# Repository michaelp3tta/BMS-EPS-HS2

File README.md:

# BMS-EPS-HS2
Repository of the HS-2 Battery Management System

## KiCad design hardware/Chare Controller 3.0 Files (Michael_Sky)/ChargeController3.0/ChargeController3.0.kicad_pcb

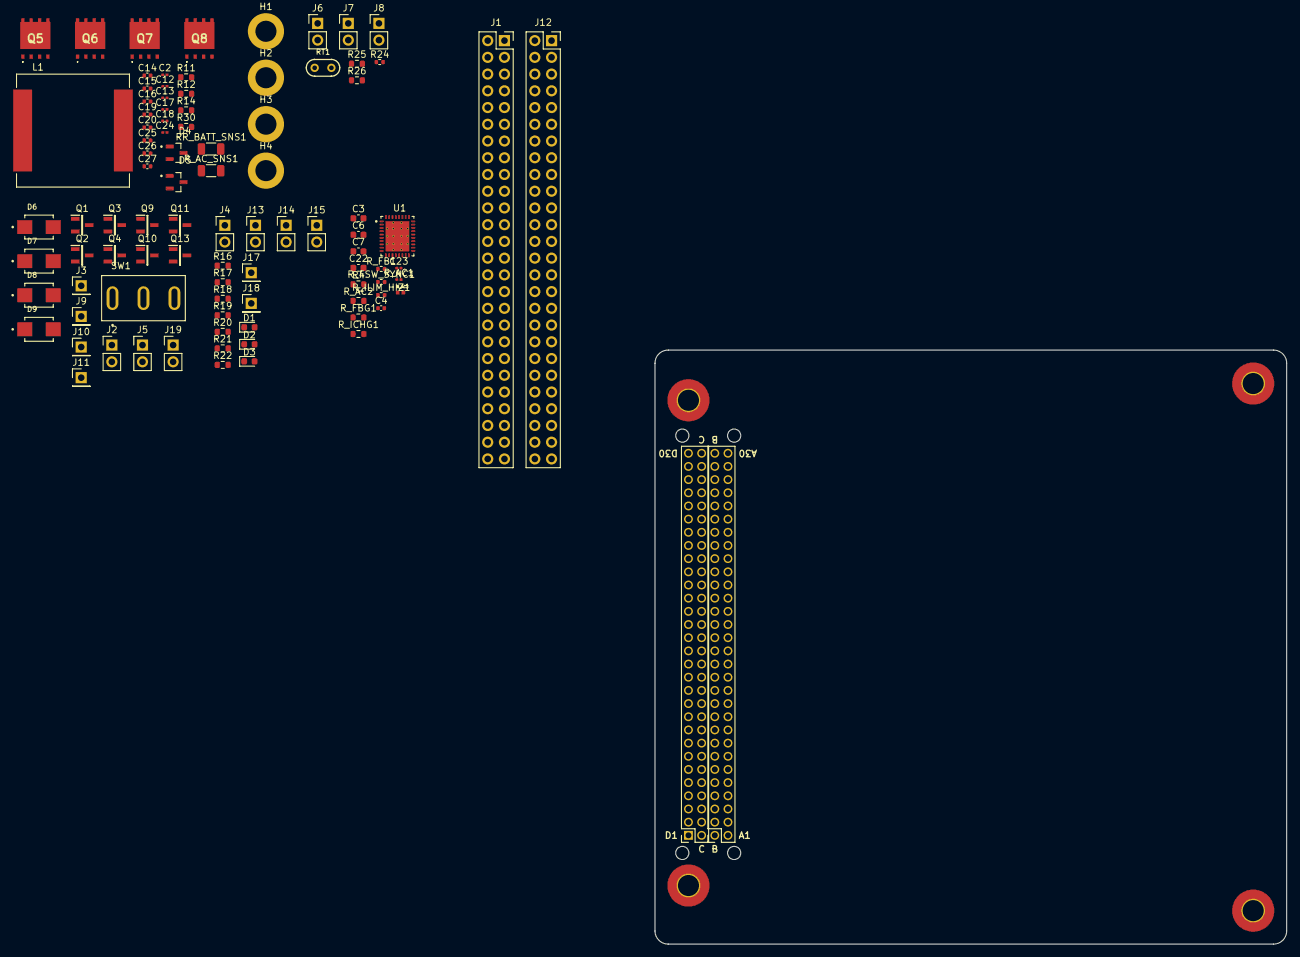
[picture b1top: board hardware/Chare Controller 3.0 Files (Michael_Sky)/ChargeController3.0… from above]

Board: 2 copper layers, 95.9 x 90.2 mm, 102 parts (0 on the bottom side), 56 nets, no tracks yet.

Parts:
C2, C12, C13, C17, C18, C24: 56u; C_0201_0603Metric
C3, C7, C22: 4.7u; C_0603_1608Metric
C4, C14, C16, C19, C20, C25, C27: 100n; C_0402_1005Metric
C6: 47u; C_0603_1608Metric
C15, C26: 470n; C_0402_1005Metric
C23: 1u; C_0201_0603Metric
D1, D2, D3: GREEN; LED_0603_1608Metric
D4, D5: BAT54
D6, D7, D8, D9: SS24
H1, H2, H3, H4: MountingHole_Pad; MountingHole_3.2mm_M3_ISO14580_Pad
H1#2, H2#2, H3#2, H4#2: MountingHole_Pad; MountingHole_3.2mm_M3_Pad_TopBottom
H5, H6, H7, H8: MountingHole; MountingHole_2mm
J1, J2: Conn_02x30_Row_Letter_First; PinSocket_2x30_P2.00mm_Vertical
J1#2, J12: Conn_02x26_Odd_Even; PinSocket_2x26_P2.54mm_Vertical
J2#2: SP_01x02_Pin; PinHeader_1x02_P2.54mm_Vertical
J3: BATT_TEST_01x01_Pin; PinHeader_1x01_P2.54mm_Vertical
J4: 3.3V_PULLUP_01x02_Pin; PinHeader_1x02_P2.54mm_Vertical
J5: BATT_01x02_Pin; PinHeader_1x02_P2.54mm_Vertical
J6, J7, J8, J13, J14, J15: Conn-1x2; PinHeader_1x02_P2.54mm_Vertical
J9: SYS_TEST_01x01_Pin; PinHeader_1x01_P2.54mm_Vertical
J10: SOL_TEST_01x01_Pin; PinHeader_1x01_P2.54mm_Vertical
J11: GND_TEST_01x01_Pin; PinHeader_1x01_P2.54mm_Vertical
J17: SCL_MAS_01x01_Pin; PinHeader_1x01_P2.54mm_Vertical
J18: SDA_MAS_01x01_Pin; PinHeader_1x01_P2.54mm_Vertical
J19: SYS-1x2; PinHeader_1x02_P2.54mm_Vertical
L1: IHLP6767GZER100M01; IND_IHLP6767GZER100M01
Q1, Q2, Q3, Q4, Q9, Q10, Q11, Q13: SI2318CDS-T1-GE3
Q5, Q6, Q7, Q8: AONS66614; AON6482
R4, R11, R12, R14, R30: 10; R_0603_1608Metric
R16, R17, R18, R19, R20, R21, R22, R26: 10k; R_0603_1608Metric
R24: 30.1k; R_0402_1005Metric
R25: 5.23k; R_0603_1608Metric
RR_BATT_SNS1: 5m; R_1206_3216Metric
RT1: 103AT-2
R_AC1: 1M; R_0201_0603Metric
R_AC2: 11.83k; R_0603_1608Metric
R_AC3: RC0402FR-0753K6L
R_AC_SNS1: 5m; R_1206_3216Metric
R_FB1: 249k; R_0402_1005Metric
R_FBG1: 16.67k; R_0603_1608Metric
R_FSW_SYNC1: 40k; R_0402_1005Metric
R_ICHG1: 16.67k; R_0603_1608Metric
R_ILIM_HIZ1: 25k; R_0402_1005Metric
SW1: 100SP1T1B1M1QEH; SW_100SP1T1B1M1QEH
U1: BQ25756ERRVR; IC_BQ25756ERRVR

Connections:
5V_PERM: J1#2.25, J1#2.26, J12.25, J12.26
/BQ25756E/ACOV: R_AC2.2, R_AC3.1, U1.35 (ACOV)
/BQ25756E/ACUV: R_AC1.2, R_AC2.1, U1.34 (ACUV)
/BQ25756E/FB: R_FB1.2, R_FBG1.1, U1.12 (FB)
/BQ25756E/FBG: R_FBG1.2, U1.11 (FBG)
/Inhibits, Inputs/EN: Q1.1, Q2.1, Q3.1, Q4.1, Q9.1, Q10.1, Q11.1, Q13.1, SW1.1
ACN: C26.2, C27.2, R30.2, U1.29 (ACN)
ACP: C25.2, C26.1, R11.2, U1.30 (ACP)
BTST_1: C19.2, D5.3, U1.26 (BTST1)
BTST_2: C20.2, D4.3, U1.20 (BTST2)
CE: J13.2, R18.1, U1.7 (~CE)
CHARGE: J1#2.31, J1#2.32
DRV_SUP: C3.1, C22.1, D4.1, D5.1, J7.1, U1.23 (DRV_SUP), U1.24 (REGN)
GND: C2.2, C3.2, C4.2, C6.2, C7.2, C12.2, C13.2, C14.1, C16.1, C17.2, C18.2, C22.2, C23.2, C24.2, C25.1, C27.1, H1.1, H1#2.1, H2.1, H2#2.1, H3.1, H3#2.1, H4.1, H4#2.1, J1#2.33, J1#2.34, J2#2.2, J4.2, J8.2, J11.1, J12.29, J12.30, J12.31, J12.32, J13.1, J19.2, Q7.1 (S_1), Q7.2 (S_2), Q7.3 (S_3), Q8.1 (S_1), Q8.2 (S_2), Q8.3 (S_3), Q9.3, Q13.2, R24.1, R26.1, R_AC3.2, R_FSW_SYNC1.1, R_ICHG1.1, R_ILIM_HIZ1.1, SW1.3
HIDRV_1: Q5.4 (G), U1.27 (HIDRV1)
HIDRV_2: Q6.4 (G), U1.19 (HIDRV2)
INT: J14.1, U1.3 (~INT)
LODRV_1: Q7.4 (G), U1.25 (LODRV1)
LODRV_2: Q8.4 (G), U1.21 (LODRV2)
unnamed: C6.1, R4.2
unnamed: D1.2 (A), R19.1
unnamed: D2.2 (A), R21.1
unnamed: D2.1 (K), J15.2
unnamed: D3.2 (A), R22.1
unnamed: D6.C, D7.A, Q1.3
unnamed: D7.C, D9.C, SW1.2
unnamed: D8.C, D9.A
unnamed: J4.1, R16.2, R17.2, R18.2, R19.2, R20.2, R21.2, R22.2
unnamed: J5.2, Q4.3
unnamed: J6.2, R26.2
unnamed: J7.2, R25.2
unnamed: J8.1, RT1.2
unnamed: D6.A, J2#2.1, J10.1
unnamed: J14.2, R20.1
unnamed: J9.1, J19.1, Q10.3
unnamed: Q1.2, Q2.3
unnamed: Q4.2, Q9.2
unnamed: C12.1, Q5.5 (D_1), Q5.6 (D_2), Q5.7 (D_3), Q5.8 (D_4), Q5.9 (D_5), R30.1, R_AC_SNS1.1
unnamed: C24.1, Q6.5 (D_1), Q6.6 (D_2), Q6.7 (D_3), Q6.8 (D_4), Q6.9 (D_5), R12.1, RR_BATT_SNS1.2
unnamed: Q10.2, Q11.2
unnamed: R_FSW_SYNC1.2, U1.36 (FSW_SYNC)
unnamed: R_ICHG1.2, U1.9 (ICHG)
unnamed: R_ILIM_HIZ1.2, U1.10 (ILIM_HIZ)
PG: D1.1 (K), U1.6 (~PG)
PGND: Q13.3, U1.17 (PGND), U1.22 (PGND), U1.37 (PGND)
SCL: J1#2.10, J17.1, R16.1, U1.1 (SCL)
SDA: J18.1, R17.1, U1.2 (SDA)
SOL: C2.1, C4.1, C7.1, C13.1, C23.1, J12.44, Q2.2, Q3.2, R4.1, R11.1, R_AC1.1, R_AC_SNS1.2, U1.32 (VAC), U1.33 (VAC)
SRN: C15.2, C16.2, R14.2, U1.13 (SRN)
SRP: C14.2, C15.1, R12.2, U1.14 (SRP)
STAT_1: J15.1, U1.4 (STAT1)
STAT_2: D3.1 (K), U1.5 (STAT2)
SW1: C19.1, L1.1, Q5.1 (S_1), Q5.2 (S_2), Q5.3 (S_3), Q7.5 (D_1), Q7.6 (D_2), Q7.7 (D_3), Q7.8 (D_4), Q7.9 (D_5), U1.28 (SW1)
SW2: C20.1, L1.2, Q6.1 (S_1), Q6.2 (S_2), Q6.3 (S_3), Q8.5 (D_1), Q8.6 (D_2), Q8.7 (D_3), Q8.8 (D_4), Q8.9 (D_5), U1.18 (SW2)
SYS/BATT: C17.1, C18.1, D8.A, J3.1, J5.1, J12.46, Q3.3, Q11.3, R14.1, RR_BATT_SNS1.1, R_FB1.1
TS: J6.1, R24.2, R25.1, RT1.1, U1.8 (TS)

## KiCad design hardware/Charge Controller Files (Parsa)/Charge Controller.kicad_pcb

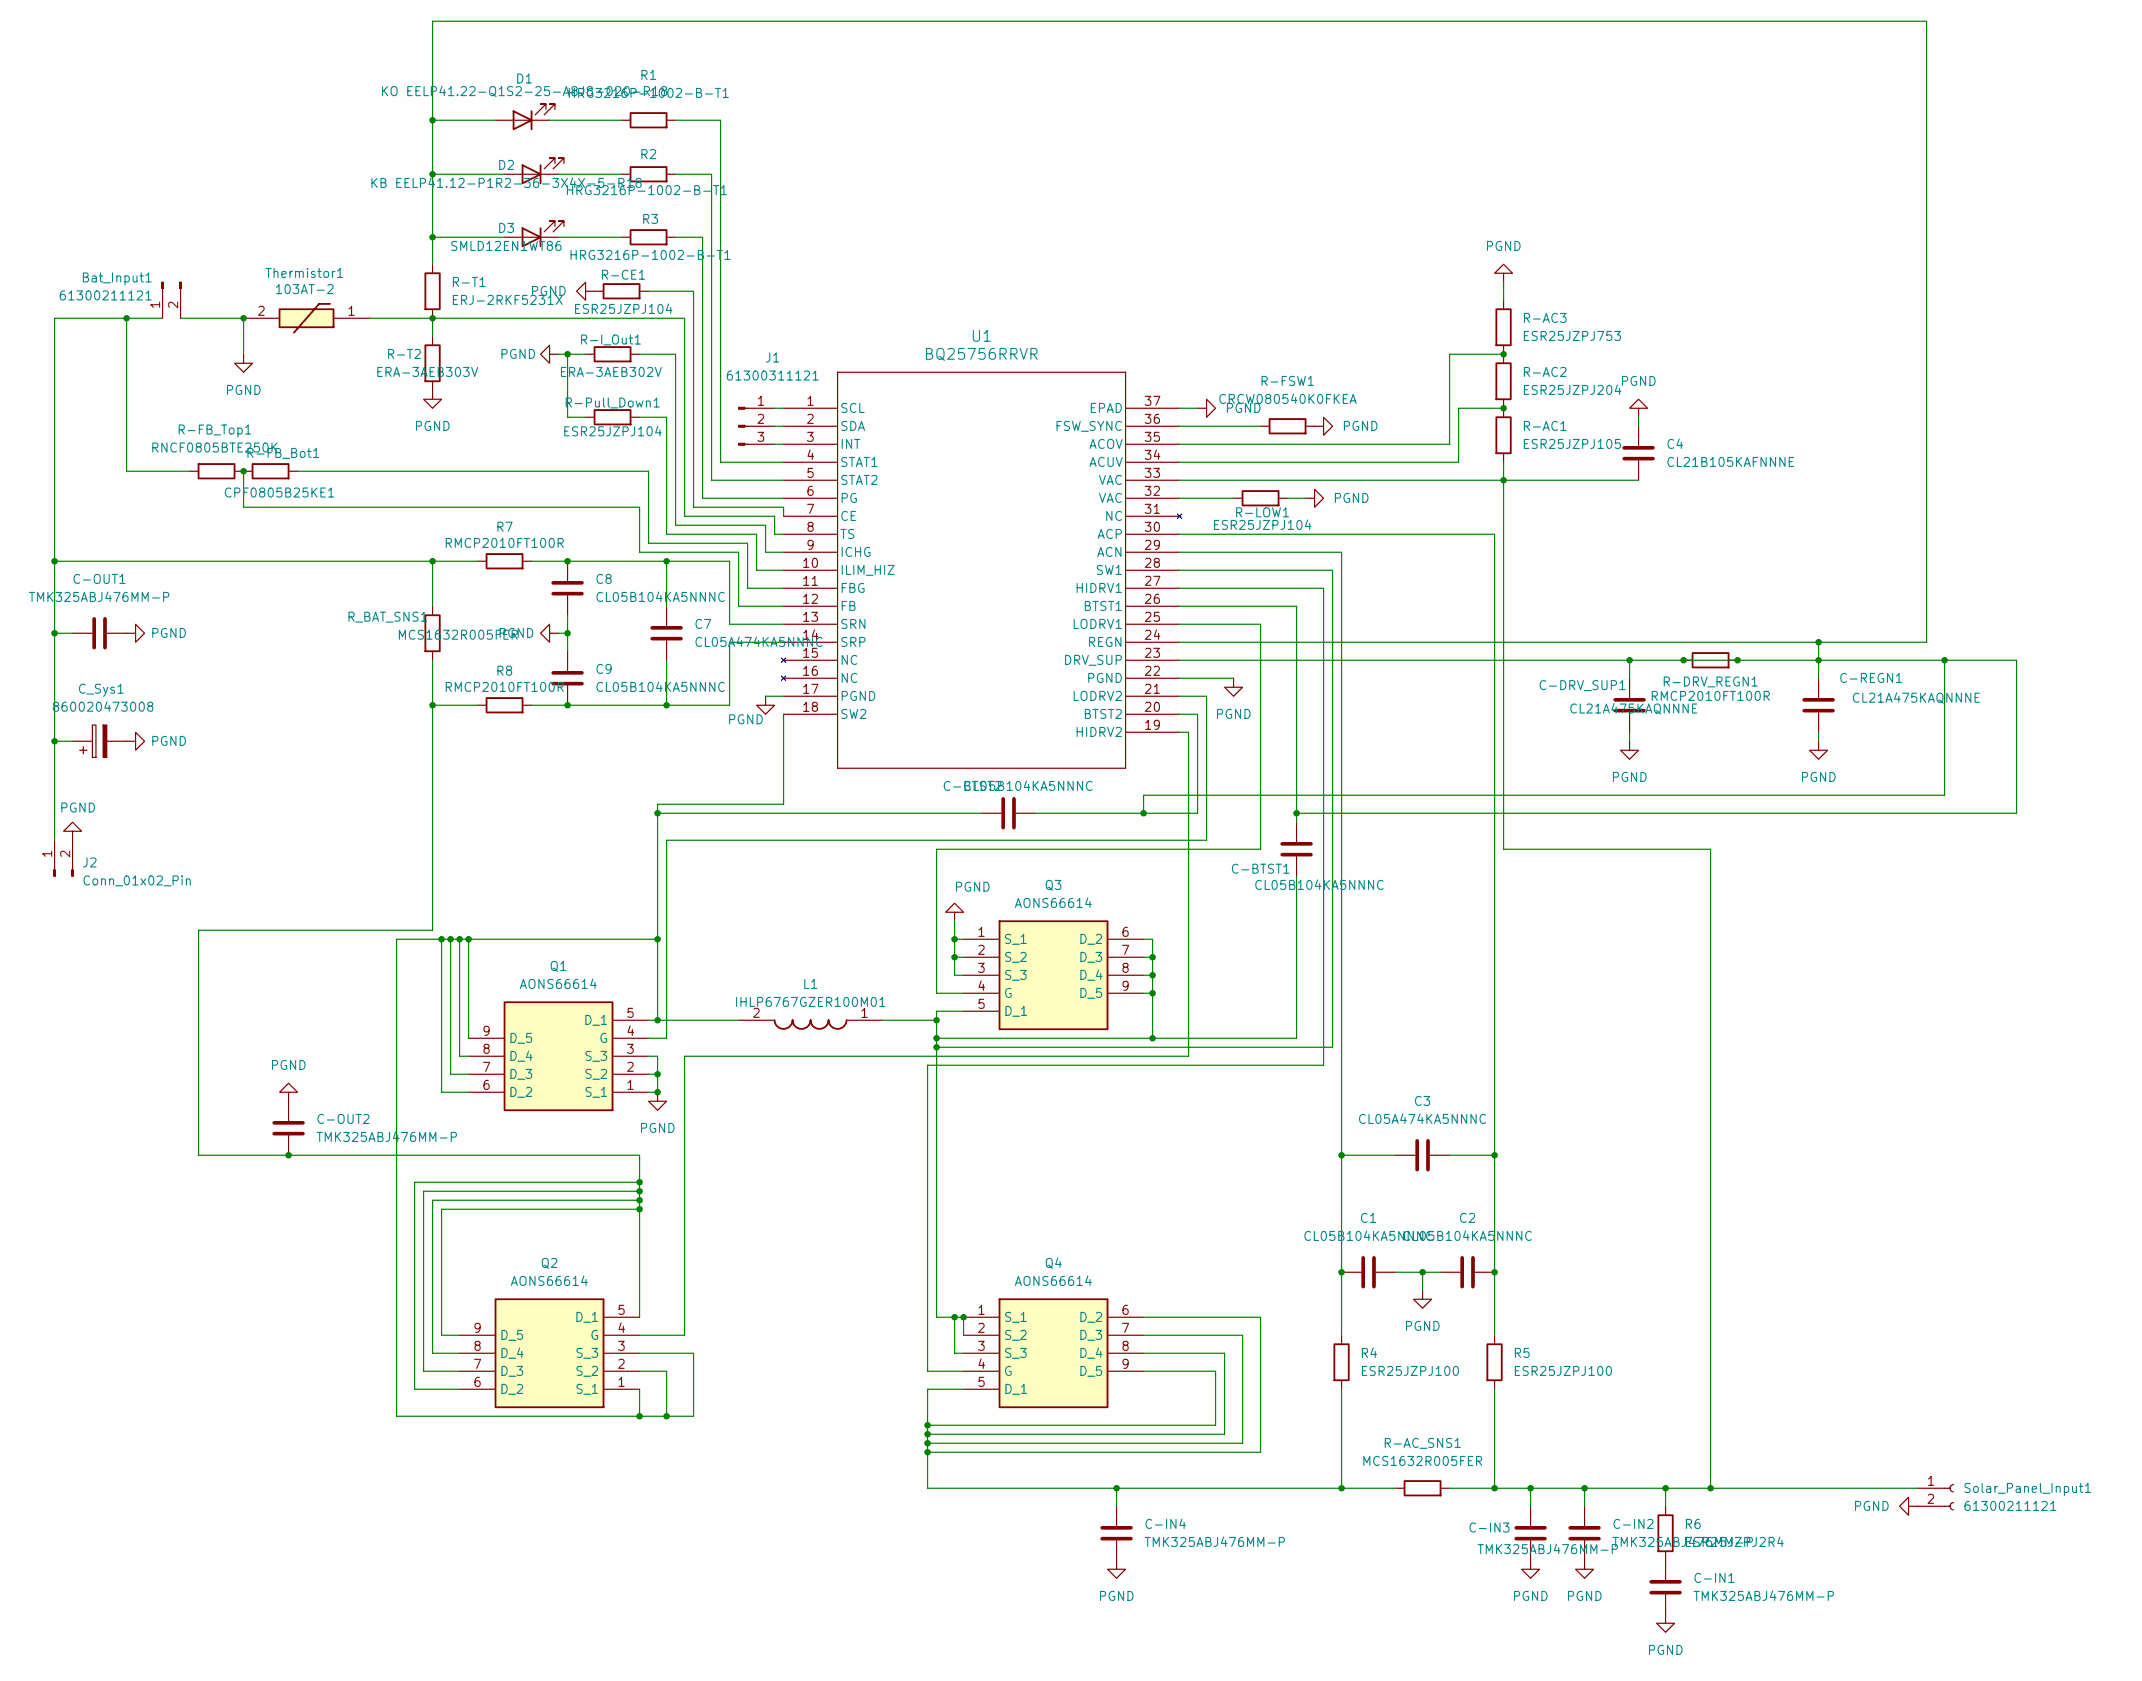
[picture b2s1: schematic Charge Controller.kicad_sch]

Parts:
Bat_Input1: 61300211121; PinHeader_1x02_P2.54mm_Vertical
C1, C2, C8, C9: CL05B104KA5NNNC; C_0402_1005Metric_Pad0.74x0.62mm_HandSolder
C3, C7: CL05A474KA5NNNC; C_0402_1005Metric_Pad0.74x0.62mm_HandSolder
C4: CL21B105KAFNNNE; C_0805_2012Metric_Pad1.18x1.45mm_HandSolder
C-BTST1, C-BTST2: CL05B104KA5NNNC; C_0402_1005Metric_Pad0.74x0.62mm_HandSolder
C-DRV_SUP1: CL21A475KAQNNNE; C_0805_2012Metric_Pad1.18x1.45mm_HandSolder
C-IN1, C-IN2, C-IN3, C-IN4: TMK325ABJ476MM-P; C_1210_3225Metric_Pad1.33x2.70mm_HandSolder
C-OUT1, C-OUT2: TMK325ABJ476MM-P; C_1210_3225Metric_Pad1.33x2.70mm_HandSolder
C-REGN1: CL21A475KAQNNNE; C_0805_2012Metric_Pad1.18x1.45mm_HandSolder
C_Sys1: 860020473008; CP_Radial_D6.3mm_P2.50mm
D1: KO EELP41.22-Q1S2-25-A8J8-020-R18; LED_0603_1608Metric_Pad1.05x0.95mm_HandSolder
D2: KB EELP41.12-P1R2-36-3X4X-5-R18; LED_0603_1608Metric_Pad1.05x0.95mm_HandSolder
D3: SMLD12EN1WT86; LED_0603_1608Metric_Pad1.05x0.95mm_HandSolder
J1: 61300311121; PinSocket_1x03_P2.54mm_Vertical
J2: Conn_01x02_Pin; PinSocket_1x02_P2.54mm_Vertical
L1: IHLP6767GZER100M01; INDPM172172X700N; Manufacturer_Part_Number IHLP6767GZER100M01
Q1, Q2, Q3, Q4: AONS66614; AON6482; Manufacturer_Part_Number AONS66614
R1, R2, R3: HRG3216P-1002-B-T1; R_1206_3216Metric_Pad1.30x1.75mm_HandSolder
R4, R5: ESR25JZPJ100; R_1210_3225Metric_Pad1.30x2.65mm_HandSolder
R6: ESR25JZPJ2R4; R_1210_3225Metric_Pad1.30x2.65mm_HandSolder
R7, R8: RMCP2010FT100R; R_2010_5025Metric_Pad1.40x2.65mm_HandSolder
R-AC1: ESR25JZPJ105; R_1210_3225Metric_Pad1.30x2.65mm_HandSolder
R-AC2: ESR25JZPJ204; R_1210_3225Metric_Pad1.30x2.65mm_HandSolder
R-AC3: ESR25JZPJ753; R_1210_3225Metric_Pad1.30x2.65mm_HandSolder
R-AC_SNS1: MCS1632R005FER; R_1206_3216Metric_Pad1.30x1.75mm_HandSolder
R-CE1: ESR25JZPJ104; R_1210_3225Metric_Pad1.30x2.65mm_HandSolder
R-DRV_REGN1: RMCP2010FT100R; R_2010_5025Metric_Pad1.40x2.65mm_HandSolder
R-FB_Bot1: CPF0805B25KE1; R_0805_2012Metric_Pad1.20x1.40mm_HandSolder
R-FB_Top1: RNCF0805BTE250K; R_0805_2012Metric_Pad1.20x1.40mm_HandSolder
R-FSW1: CRCW080540K0FKEA; R_0805_2012Metric_Pad1.20x1.40mm_HandSolder
R-I_Out1: ERA-3AEB302V; R_0603_1608Metric_Pad0.98x0.95mm_HandSolder
R-LOW1: ESR25JZPJ104; R_1210_3225Metric_Pad1.30x2.65mm_HandSolder
R-Pull_Down1: ESR25JZPJ104; R_1210_3225Metric_Pad1.30x2.65mm_HandSolder
R-T1: ERJ-2RKF5231X; R_0402_1005Metric_Pad0.72x0.64mm_HandSolder
R-T2: ERA-3AEB303V; R_0603_1608Metric_Pad0.98x0.95mm_HandSolder
R_BAT_SNS1: MCS1632R005FER; R_1206_3216Metric_Pad1.30x1.75mm_HandSolder
Solar_Panel_Input1: 61300211121; PinSocket_1x02_P2.54mm_Vertical
Thermistor1: 103AT-2; 103AT2; Mouser Part Number 954-103AT-2
U1: BQ25756RRVR; VQFN36_RRV_TEX

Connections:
unnamed: Bat_Input1.1, C-OUT1.1, C_Sys1.1, J2.1, R7.1, R-FB_Top1.2, R_BAT_SNS1.1
unnamed: C-IN1.1, R6.2
unnamed: C-BTST1.1, C-BTST2.2, C-DRV_SUP1.1, C-REGN1.1, D1.2 (A), D2.2 (A), D3.2 (A), R-DRV_REGN1.1, R-DRV_REGN1.2, R-T1.1, U1.20 (BTST2), U1.23 (DRV_SUP), U1.24 (REGN), U1.26 (BTST1)
unnamed: D1.1 (K), R1.1
unnamed: D2.1 (K), R2.1
unnamed: D3.1 (K), R3.1
unnamed: J1.1, U1.1 (SCL)
unnamed: J1.2, U1.2 (SDA)
unnamed: J1.3, U1.3 (INT)
unnamed: C-BTST2.1, L1.2, Q1.5 (D_1), Q1.6 (D_2), Q1.7 (D_3), Q1.8 (D_4), Q1.9 (D_5), Q2.1 (S_1), Q2.2 (S_2), Q2.3 (S_3), U1.18 (SW2)
unnamed: Q1.4 (G), U1.21 (LODRV2)
unnamed: C-OUT2.2, Q2.5 (D_1), Q2.6 (D_2), Q2.7 (D_3), Q2.8 (D_4), Q2.9 (D_5), R8.1, R_BAT_SNS1.2
unnamed: Q2.4 (G), U1.19 (HIDRV2)
unnamed: C-BTST1.2, L1.1, Q3.5 (D_1), Q3.6 (D_2), Q3.7 (D_3), Q3.8 (D_4), Q3.9 (D_5), Q4.1 (S_1), Q4.2 (S_2), Q4.3 (S_3), U1.28 (SW1)
unnamed: Q3.4 (G), U1.25 (LODRV1)
unnamed: C-IN4.2, Q4.5 (D_1), Q4.6 (D_2), Q4.7 (D_3), Q4.8 (D_4), Q4.9 (D_5), R4.2, R-AC_SNS1.1
unnamed: Q4.4 (G), U1.27 (HIDRV1)
unnamed: R-LOW1.1, U1.32 (VAC)
unnamed: C4.2, C-IN2.1, C-IN3.1, R5.2, R6.1, R-AC1.2, R-AC_SNS1.2, Solar_Panel_Input1.1, U1.33 (VAC)
unnamed: C1.1, C3.1, R4.1, U1.29 (ACN)
unnamed: R-AC2.1, R-AC3.2, U1.35 (ACOV)
unnamed: C2.2, C3.2, R5.1, U1.30 (ACP)
unnamed: R-AC1.1, R-AC2.2, U1.34 (ACUV)
unnamed: R-CE1.2, U1.7 (CE)
unnamed: R-FB_Bot1.1, R-FB_Top1.1, U1.12 (FB)
unnamed: R-FB_Bot1.2, U1.11 (FBG)
unnamed: R-FSW1.1, U1.36 (FSW_SYNC)
unnamed: R-I_Out1.2, U1.9 (ICHG)
unnamed: R-Pull_Down1.2, U1.10 (ILIM_HIZ)
unnamed: R3.2, U1.6 (PG)
unnamed: C7.1, C8.1, R7.2, U1.13 (SRN)
unnamed: C7.2, C9.2, R8.2, U1.14 (SRP)
unnamed: R1.2, U1.4 (STAT1)
unnamed: R2.2, U1.5 (STAT2)
unnamed: R-T1.2, R-T2.1, Thermistor1.1, U1.8 (TS)
PGND: Bat_Input1.2, C1.2, C2.1, C4.1, C8.2, C9.1, C-DRV_SUP1.2, C-IN1.2, C-IN2.2, C-IN3.2, C-IN4.1, C-OUT1.2, C-OUT2.1, C-REGN1.2, C_Sys1.2, J2.2, Q1.1 (S_1), Q1.2 (S_2), Q1.3 (S_3), Q3.1 (S_1), Q3.2 (S_2), Q3.3 (S_3), R-AC3.1, R-CE1.1, R-FSW1.2, R-I_Out1.1, R-LOW1.2, R-Pull_Down1.1, R-T2.2, Solar_Panel_Input1.2, Thermistor1.2, U1.17 (PGND), U1.22 (PGND), U1.37 (EPAD)

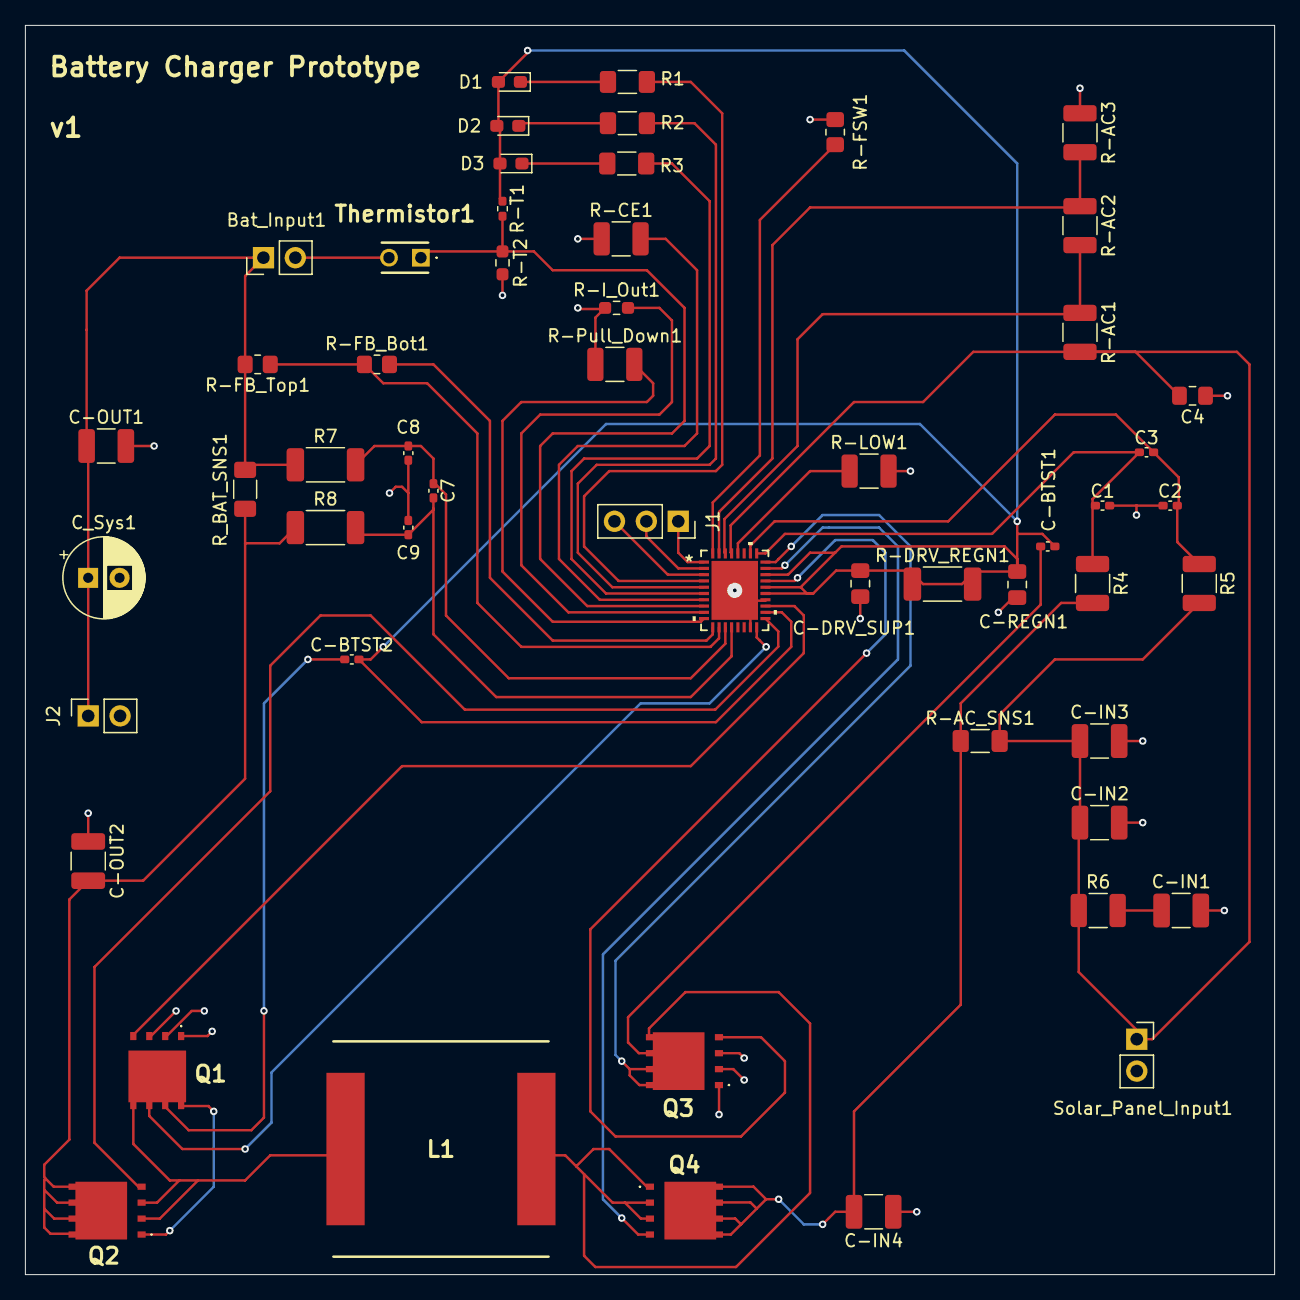
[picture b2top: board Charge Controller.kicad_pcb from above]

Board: 2 copper layers, 99.5 x 99.5 mm, 55 parts (0 on the bottom side), 36 nets.

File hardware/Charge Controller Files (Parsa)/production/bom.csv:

Designator,Footprint,Quantity,Value,LCSC Part #
Bat_Input1,PinHeader_1x02_P2.54mm_Vertical,1,61300211121,
"C-BTST1, C-BTST2, C1, C2, C8, C9",0402,6,CL05B104KA5NNNC,
"C-DRV_SUP1, C-REGN1",0805,2,CL21A475KAQNNNE,
"C-IN1, C-IN2, C-IN3, C-IN4, C-OUT1, C-OUT2",1210,6,TMK325ABJ476MM-P,
"C3, C7",0402,2,CL05A474KA5NNNC,
C4,0805,1,CL21B105KAFNNNE,
C_Sys1,CP_Radial_D6.3mm_P2.50mm,1,860020473008,
D1,0603,1,KO EELP41.22-Q1S2-25-A8J8-020-R18,
D2,0603,1,KB EELP41.12-P1R2-36-3X4X-5-R18,
D3,0603,1,SMLD12EN1WT86,
J1,PinSocket_1x03_P2.54mm_Vertical,1,61300311121,
J2,PinSocket_1x02_P2.54mm_Vertical,1,Conn_01x02_Pin,
L1,INDPM172172X700N,1,IHLP6767GZER100M01,
"Q1, Q2, Q3, Q4",AON6482,4,AONS66614,
R-AC1,1210,1,ESR25JZPJ105,
R-AC2,1210,1,ESR25JZPJ204,
R-AC3,1210,1,ESR25JZPJ753,
"R-AC_SNS1, R_BAT_SNS1",1206,2,MCS1632R005FER,
"R-CE1, R-LOW1, R-Pull_Down1",1210,3,ESR25JZPJ104,
"R-DRV_REGN1, R7, R8",2010,3,RMCP2010FT100R,
R-FB_Bot1,0805,1,CPF0805B25KE1,
R-FB_Top1,0805,1,RNCF0805BTE250K,
R-FSW1,0805,1,CRCW080540K0FKEA,
R-I_Out1,0603,1,ERA-3AEB302V,
R-T1,0402,1,ERJ-2RKF5231X,
R-T2,0603,1,ERA-3AEB303V,
"R1, R2, R3",1206,3,HRG3216P-1002-B-T1,
"R4, R5",1210,2,ESR25JZPJ100,
R6,1210,1,ESR25JZPJ2R4,
Solar_Panel_Input1,PinSocket_1x02_P2.54mm_Vertical,1,61300211121,
Thermistor1,103AT2,1,103AT-2,
U1,VQFN36_RRV_TEX,1,BQ25756RRVR,

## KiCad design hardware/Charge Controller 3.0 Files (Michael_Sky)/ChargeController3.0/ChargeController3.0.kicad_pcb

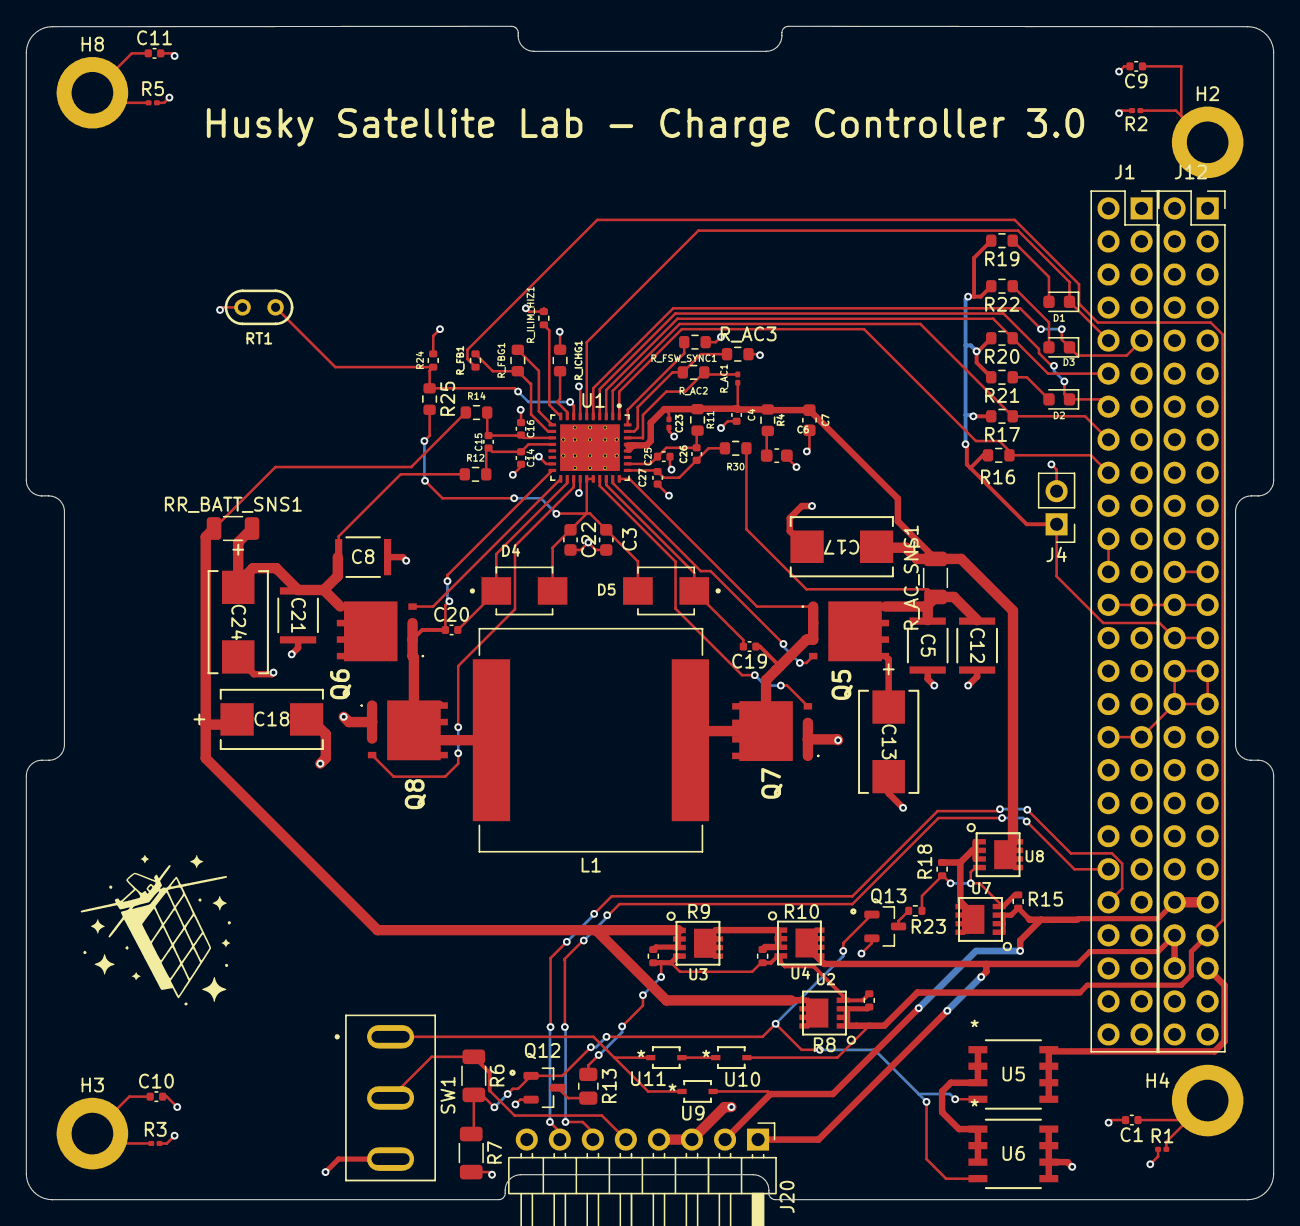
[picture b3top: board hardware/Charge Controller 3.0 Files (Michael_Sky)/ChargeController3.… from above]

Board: 2 copper layers, 95.9 x 90.2 mm, 95 parts (0 on the bottom side), 61 nets.

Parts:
C1, C9, C10, C11: 100nF; C_0402_1005Metric
C3, C7, C22: 4.7u; C_0603_1608Metric
C4, C14, C16, C19, C20, C25, C27: 100n; C_0402_1005Metric
C5, C8, C12, C21: 10u; CGA6P1X7R1N106K250AC
C6: 47u; C_0603_1608Metric
C13, C17, C18, C24: 100u; T520D107
C15, C26: 470n; C_0402_1005Metric
C23: 1u; C_0201_0603Metric
D1, D2, D3: GREEN; LED_0603_1608Metric
D4, D5: DIOM4336X265N; SS26
H2, H3, H4, H8: MountingHole_Pad; MountingHole_3.2mm_M3_ISO14580_Pad
J1, J12: Conn_02x26_Odd_Even; PinSocket_2x26_P2.54mm_Vertical
J4: 3.3V_PULLUP_01x02_Pin; PinHeader_1x02_P2.54mm_Vertical
J20: Conn_01x08_Pin; PinHeader_1x08_P2.54mm_Horizontal
L1: IHLP6767GZER100M01; IND_IHLP6767GZER100M01
Q5, Q6, Q7, Q8: AONS66614; AON6482
Q12, Q13: SOT91P240X110-3N; 2N7002K-7
R1, R2, R3, R5: 1M; R_0201_0603Metric
R4, R11, R12, R14, R30: 10; R_0603_1608Metric
R6: 330k; R_1206_3216Metric
R7: 470k; R_1206_3216Metric
R8, R9, R10, R15, R18: 1M; R_0402_1005Metric
R13: 400k; R_0805_2012Metric
R16, R17, R19, R20, R21, R22: 10k; R_0603_1608Metric
R23: 200k; R_0402_1005Metric
R24: 30.1k; R_0402_1005Metric
R25: 5.23k; R_0603_1608Metric
RR_BATT_SNS1: 5m; R_1206_3216Metric
RT1: 103AT-2
R_AC1: 1M; R_0201_0603Metric
R_AC2: 40.2k; R_0603_1608Metric
R_AC3: 60.4k; R_0603_1608Metric
R_AC_SNS1: 5m; R_1206_3216Metric
R_FB1: 249k; R_0402_1005Metric
R_FBG1: 16.2k; R_0603_1608Metric
R_FSW_SYNC1: 133k; R_0603_1608Metric
R_ICHG1: 16.67k; R_0603_1608Metric
R_ILIM_HIZ1: 25k; R_0402_1005Metric
SW1: 100SP1T1B1M1QEH; SW_100SP1T1B1M1QEH
U1: BQ25756ERRVR; IC_BQ25756ERRVR
U2, U3, U4, U7, U8: SISH101DN-T1-GE3; SISH
U5, U6: SI4122DY-T1-GE3; SI4122.
U9, U10, U11: BAT46WJ_115; BAT46WJ115

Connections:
3.3V: J4.1, J12.27, J12.28, R16.2, R17.2, R19.2, R20.2, R21.2, R22.2
5V_PERM: J1.25, J1.26, J12.25, J12.26
12V: J12.23, J12.24
/BQ25756E/ACOV: R_AC2.2, R_AC3.1, U1.35 (ACOV)
/BQ25756E/ACUV: R_AC1.2, R_AC2.1, U1.34 (ACUV)
/BQ25756E/FB: R_FB1.2, R_FBG1.1, U1.12 (FB)
/BQ25756E/FBG: R_FBG1.2, U1.11 (FBG)
ACN: C26.2, C27.2, R30.2, U1.29 (ACN)
ACP: C25.2, C26.1, R11.2, U1.30 (ACP)
BATT+_PIN: J12.45, R8.1, R_FB1.1, U2.1 (S), U2.2 (S), U2.3 (S), U10.2
BATT-_PIN: J12.47, U5.5, U5.6, U5.7, U5.8
BTST_1: C19.2, D5.C, U1.26 (BTST1)
BTST_2: C20.2, D4.C, U1.20 (BTST2)
DIV: Q12.1, Q13.1, R6.2, R7.1, U5.4, U6.4
DRV_SUP: C3.1, C22.1, D4.A, D5.A, R25.2, U1.23 (DRV_SUP), U1.24 (REGN)
EN: J20.5, R6.1, SW1.2
GND: C1.2, C3.2, C4.2, C5.2, C6.2, C7.2, C8.2, C9.2, C10.2, C11.2, C12.2, C13.2, C14.1, C16.1, C17.2, C18.2, C21.2, C22.2, C23.2, C24.2, C25.1, C27.1, J1.33, J1.34, J4.2, J12.29, J12.30, J12.31, J12.32, J20.3, J20.4, Q7.1 (S_1), Q7.2 (S_2), Q7.3 (S_3), Q8.1 (S_1), Q8.2 (S_2), Q8.3 (S_3), Q12.2, Q13.2, R1.2, R2.2, R3.2, R5.2, R7.2, R24.1, RT1.2, R_AC3.2, R_FSW_SYNC1.1, R_ICHG1.1, R_ILIM_HIZ1.1, SW1.3, U1.7 (~CE), U1.17 (PGND), U1.22 (PGND), U1.37 (PGND), U1.38, U1.39, U1.40, U1.41, U1.42, U1.43, U1.44, U1.45, U1.46, U1.47, U1.48, U1.49, U1.50, U1.51, U1.52, U1.53, U6.5, U6.6, U6.7, U6.8
HIDRV_1: Q5.4 (G), U1.27 (HIDRV1)
HIDRV_2: Q6.4 (G), U1.19 (HIDRV2)
IN: C4.1, C7.1, C17.1, C23.1, R4.1, R11.1, R_AC1.1, R_AC_SNS1.2, U1.32 (VAC), U1.33 (VAC), U8.5 (D), U8.6 (D), U8.7 (D), U8.8 (D), U8.PAD
INT: J1.12, R20.1, U1.3 (~INT)
LODRV_1: Q7.4 (G), U1.25 (LODRV1)
LODRV_2: Q8.4 (G), U1.21 (LODRV2)
unnamed: C1.1, H4.1 (1_1), R1.1
unnamed: C6.1, R4.2
unnamed: C9.1, H2.1 (1_1), R2.1
unnamed: C10.1, H3.1 (1_1), R3.1
unnamed: C11.1, H8.1 (1_1), R5.1
unnamed: D1.2 (A), R19.1
unnamed: D2.2 (A), R21.1
unnamed: D3.2 (A), R22.1
unnamed: C5.1, C12.1, C13.1, Q5.5 (D_1), Q5.6 (D_2), Q5.7 (D_3), Q5.8 (D_4), Q5.9 (D_5), R30.1, R_AC_SNS1.1
unnamed: C8.1, C21.1, C24.1, Q6.5 (D_1), Q6.6 (D_2), Q6.7 (D_3), Q6.8 (D_4), Q6.9 (D_5), R12.1, RR_BATT_SNS1.2
unnamed: Q12.3, R13.2
unnamed: Q13.3, R23.2
unnamed: R10.1, U3.5 (D), U3.6 (D), U3.7 (D), U3.8 (D), U3.PAD, U4.1 (S), U4.2 (S), U4.3 (S)
unnamed: R18.1, U7.5 (D), U7.6 (D), U7.7 (D), U7.8 (D), U7.PAD, U8.1 (S), U8.2 (S), U8.3 (S)
unnamed: SW1.1, U9.1, U11.1
unnamed: R_FSW_SYNC1.2, U1.36 (FSW_SYNC)
unnamed: R_ICHG1.2, U1.9 (ICHG)
unnamed: R_ILIM_HIZ1.2, U1.10 (ILIM_HIZ)
unnamed: R8.2, R9.2, R10.2, R13.1, U2.4 (G), U3.4 (G), U4.4 (G)
unnamed: U5.1, U5.2, U5.3, U6.1, U6.2, U6.3
unnamed: R15.2, R18.2, R23.1, U7.4 (G), U8.4 (G)
unnamed: U10.1, U11.2
OUT: C18.1, R9.1, R14.1, RR_BATT_SNS1.1, U2.5 (D), U2.6 (D), U2.7 (D), U2.8 (D), U2.PAD, U3.1 (S), U3.2 (S), U3.3 (S)
PG: D1.1 (K), J1.10, U1.6 (~PG)
RS-485 SYS1 B: J1.22, J1.24
SCL: J1.18, R16.1, U1.1 (SCL)
SDA: J1.16, R17.1, U1.2 (SDA)
SOL_PIN: J12.43, J12.44, J20.2, R15.1, U7.1 (S), U7.2 (S), U7.3 (S), U9.2
SRN: C15.2, C16.2, R14.2, U1.13 (SRN)
SRP: C14.2, C15.1, R12.2, U1.14 (SRP)
STAT_1: D2.1 (K), J1.14, U1.4 (STAT1)
STAT_2: D3.1 (K), J1.9, U1.5 (STAT2)
SW1: C19.1, L1.1, Q5.1 (S_1), Q5.2 (S_2), Q5.3 (S_3), Q7.5 (D_1), Q7.6 (D_2), Q7.7 (D_3), Q7.8 (D_4), Q7.9 (D_5), U1.28 (SW1)
SW2: C20.1, L1.2, Q6.1 (S_1), Q6.2 (S_2), Q6.3 (S_3), Q8.5 (D_1), Q8.6 (D_2), Q8.7 (D_3), Q8.8 (D_4), Q8.9 (D_5), U1.18 (SW2)
SYS_PIN: J12.46, J12.48, J20.1, U4.5 (D), U4.6 (D), U4.7 (D), U4.8 (D), U4.PAD
TS: R24.2, R25.1, RT1.1, U1.8 (TS)
UART_RX: J1.42, J20.6
UART_TX: J1.44, J20.7

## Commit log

2025-10-05 Initial Commit: Quarter agenda doc - mp
2025-10-05 added folder structure
2025-10-05 added both bms prototypes, useful datasheets and schematics - mp
2025-10-08 added symbol files
2025-10-13 Updated File Directory
2025-10-13 sky first commit test
2025-10-20 Design Specs I
    Update 10/20 - design specs I
2025-10-22 Design Specs Update II
    Updates Design specs and layout
2025-10-23 Design Specs III
    Design Specs III
2025-10-24 Generated BOM
2025-10-27 More design
    Design Specs IV
2025-10-27 Inhibits Draft
    Inhibits First Draft - MP
2025-10-27 Update MOSFET symbols
    Update MOSFET symbols
2025-11-02 Updates
    Added FPs, fixed ILIM_HIZ and ICHG vals, updated Inhibits system
2025-11-15 R/C name
    R/C names
2025-11-15 Change try II
    Change try II
2025-11-15 Update ChargeController2.0.csv
    generated new bom
2025-11-17 Assigned resistor footprints
2025-11-18 main
    main
2025-11-18 Updated all footprints
2025-11-18 Footprint Updates
    put BQE IC into schematic, assigned remaining footprints.
2025-11-18 Another one
    fully updated
2025-11-22 updated malfunctioning footprints/symbols
2025-11-22 BQ update
    Bq Update
2025-11-22 updated footprints
2025-11-30 First Update
    Prelim layout
2025-12-01 Diode/Small Fixes
    - Changed Inhibits MOSFETs to all be same footprint
    - Changing diodes
    - Inhibits/Power Path -> SS24
    - Bootstrap -> BAT54
    - LODRV_1 pin incorrectly placed
2025-12-01 PCB First Draft
    First Draft of PCB
    Notes:
    - Inhibits layout could use work
    - No gorund plane, unfinished
2025-12-05 PCB routing/MOSFET fix
    - PCB routing
    - MOSFET footprint fix (9 pins)
2025-12-05 PCB routing
    More PCB routing
2026-01-07 PCB fixes
    Routing fixes, removed redundent vias, fixed thermal spoke nets, changed min. annular width to 1.3.
2026-01-08 Slight fixes
    slight fixes to pbc
2026-01-09 PCB fixes
    Routing changes
2026-01-10 PCB fixes
    Changed RAC_3 symbol and footprint, changed Inhibits mosfets to later (better) version.
2026-01-16 PCB fix
    Final PCB fix
2026-02-06 Inhibits Schematic
    Inhibits schematic added to repo for review
2026-02-07 Charge Controller 3.0
    Next Prototype formatting (Schematic Format Done)
2026-02-13 fe
    fd
2026-02-13 Fix?
    Fix?
2026-02-13 Update ChargeController2.0.kicad_sch
    pcb addition
2026-02-18 Ready for Manufacturing
    Final push
2026-02-20 Mac/window fix
    mac/window fix
2026-03-13 Templates
    Templates added
2026-03-13 name change
    name cheange
2026-03-13 add pin headers
2026-03-13 push test
2026-03-21 Added header pins and started labelling outputs
2026-03-24 more label placement
2026-03-25 Formatting
    Added schematic template from librecube, attempted to fix footprint template file path issues by copying over footprints into current project library
2026-04-01 n
    new
2026-04-02 moved pins to sep page
2026-04-03 Grounding and Filtering, 3.0 Inhibits Updated
    Grounding and Filtering, 3.0 Inhibits Updated
2026-04-03 added pins and pcb template
2026-04-03 changed folder name
2026-04-10 template layout
2026-04-10 pcb template start
2026-04-18 Added template, reassigned pins
2026-04-22 Testing Pins
    Testing pins addition
2026-04-24 fixed merge :(
2026-04-25 New formatting
    New formatting
2026-05-06 Final PCB?
    inhibits rework, filtering rework
2026-05-06 mas
    mas
2026-05-08 pc104 updates
2026-05-12 Sims + Gerbers added
    Sims + Gerbers added
2026-05-13 Sims + files
    Sims + files
2026-05-20 pc104 pinout fixes
2026-05-21 librecube edits
    edits
